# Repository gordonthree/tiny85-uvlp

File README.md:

# tiny85-uvlp

Quick and dirty microcontroller based undervoltage lockout protection circuit to protect battery packs from being drawn too low. Powered from the pack, this
board is not intended for long time use with the pack. It is only intended to provide protection while pack is in use with a larger progject.

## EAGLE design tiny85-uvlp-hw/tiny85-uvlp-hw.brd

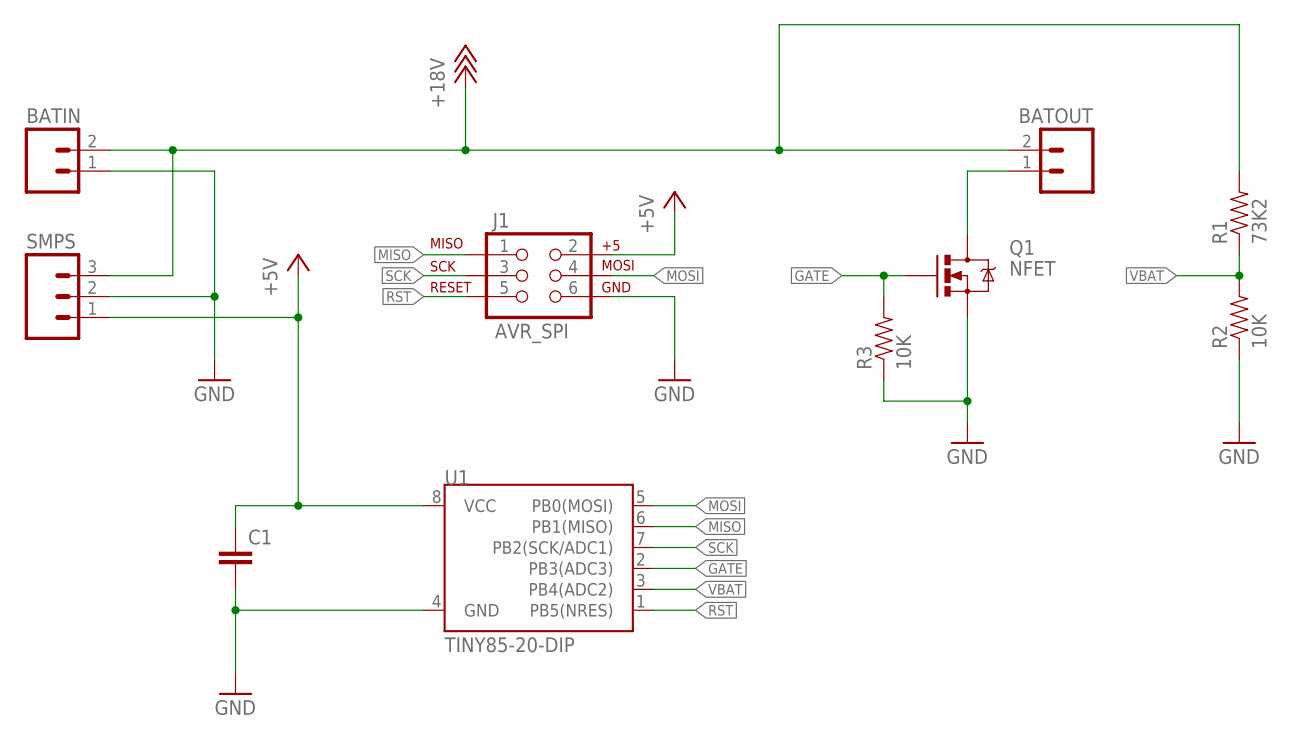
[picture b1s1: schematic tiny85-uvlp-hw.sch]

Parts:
BATIN: M02PTH3; 1X02_LONGPADS
BATOUT: M02PTH3; 1X02_LONGPADS
C1: 0.1UF-50V-20%(PTH)KIT-EZ; CAP-PTH-SMALL-KIT
J1: AVR_SPI; 2X3
Q1: NFET; TO220V
R1: 73K2; AXIAL-0.3
R2, R3: 10K; AXIAL-0.3
SMPS: M03LONGPADS; 1X03_LONGPADS
U1: TINY85-20-DIP; DIP08

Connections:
+5V: C1.1, J1.2, SMPS.1, U1.8 (VCC)
+18V: BATIN.2, BATOUT.2, R1.P$2 (2), SMPS.3
GATE: Q1.1 (G), R3.P$2 (2), U1.2 (PB3(ADC3))
GND: BATIN.1, C1.2, J1.6, Q1.3 (S), R2.P$1 (1), R3.P$1 (1), SMPS.2, U1.4 (GND)
GNDOUT: BATOUT.1, Q1.2 (D)
MISO: J1.1, U1.6 (PB1(MISO))
MOSI: J1.4, U1.5 (PB0(MOSI))
RST: J1.5, U1.1 (PB5(NRES))
SCK: J1.3, U1.7 (PB2(SCK/ADC1))
VBAT: R1.P$1 (1), R2.P$2 (2), U1.3 (PB4(ADC2))

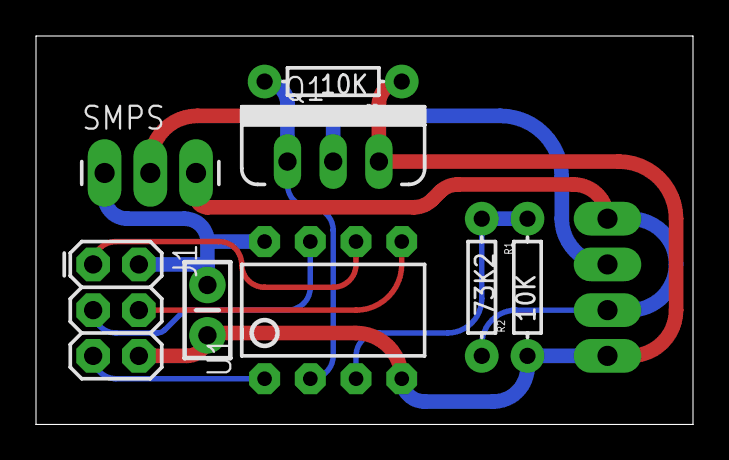
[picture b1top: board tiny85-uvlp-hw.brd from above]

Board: 2 copper layers, 36.5 x 21.6 mm, 10 parts (0 on the bottom side), 10 nets.

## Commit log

2022-08-23 first commit!
2022-08-23 Created README
    Added some details
2022-08-23 fine tune schematic and routing

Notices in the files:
parts and their libraries:
SparkFun-Connectors: Licensing: Creative Commons ShareAlike 4.0 International - https://creativecommons.org/licenses/by-sa/4.0
